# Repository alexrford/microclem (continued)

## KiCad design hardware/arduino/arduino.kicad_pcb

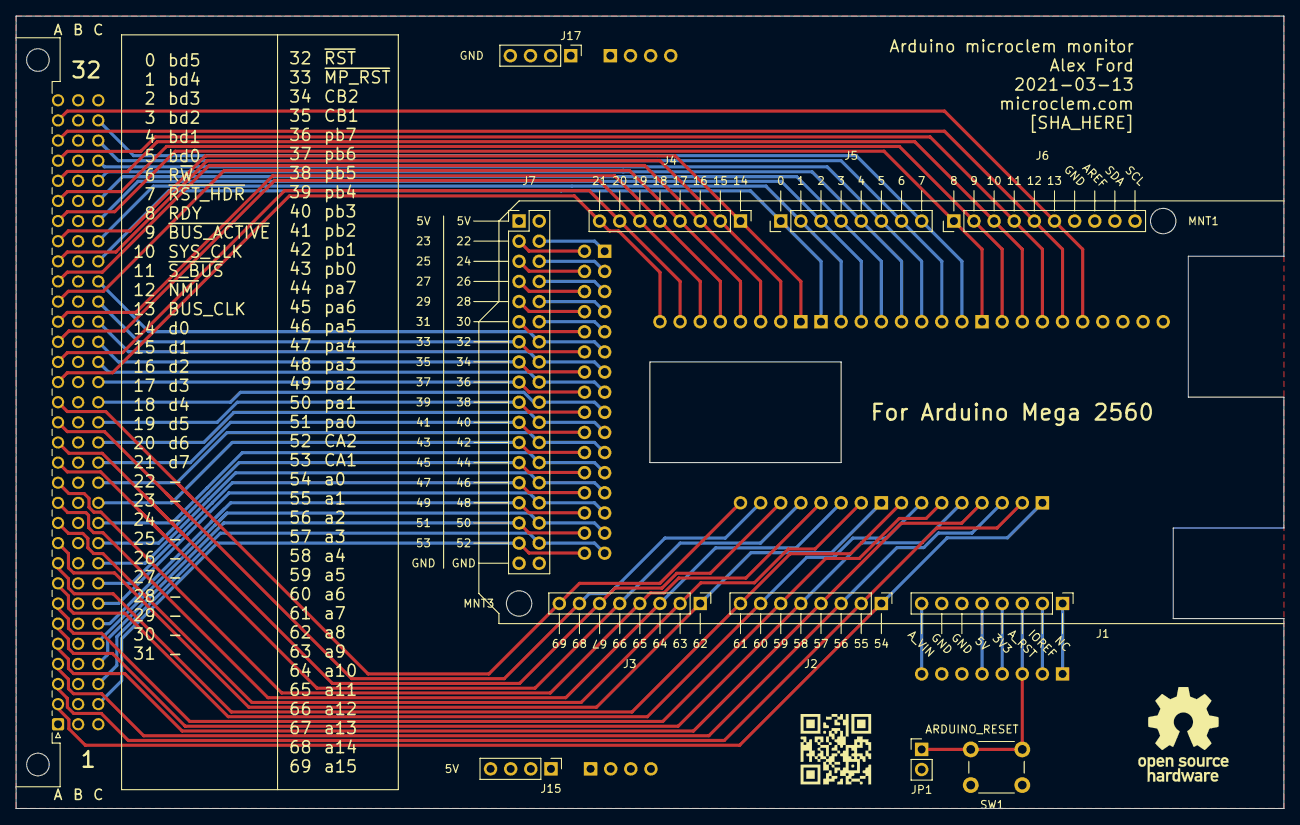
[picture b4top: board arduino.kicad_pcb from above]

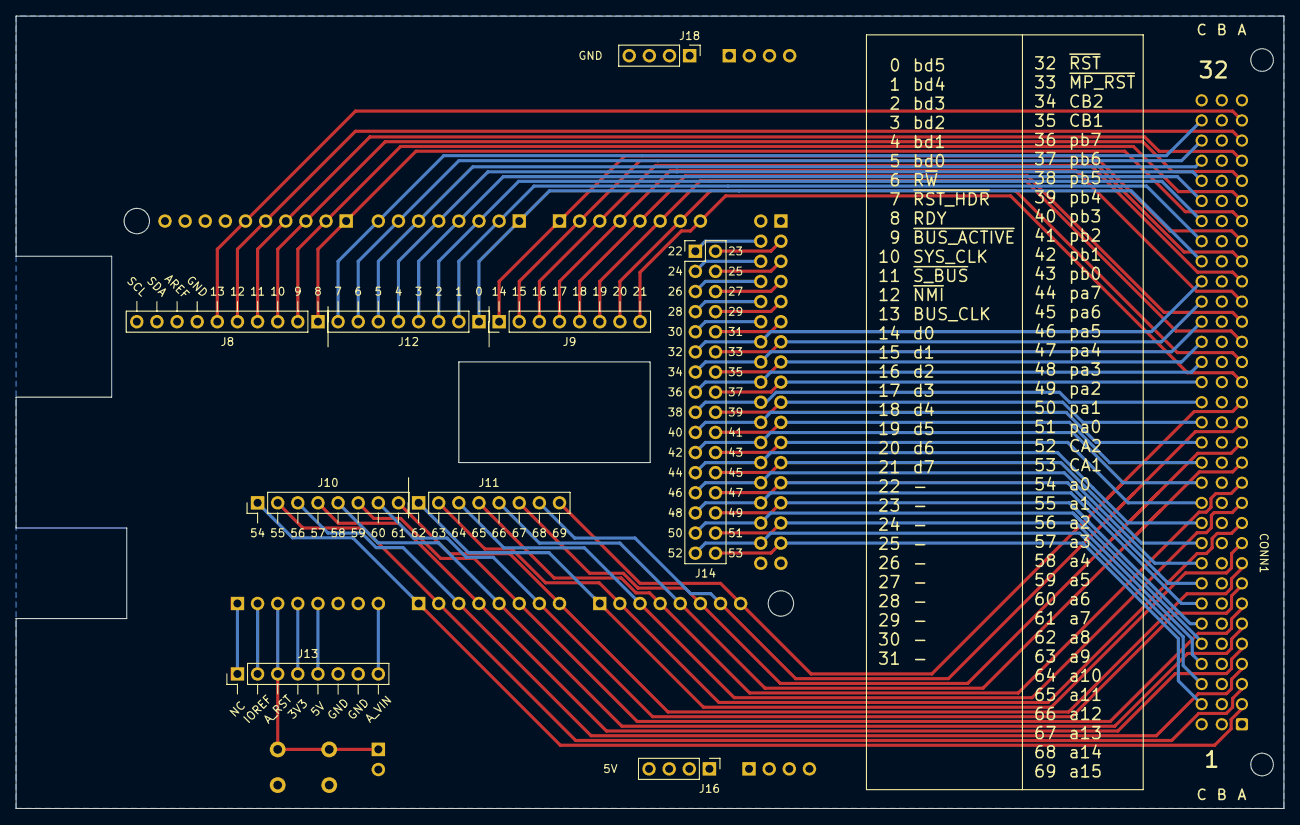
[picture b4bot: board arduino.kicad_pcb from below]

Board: 2 copper layers, 160.0 x 100.0 mm, 23 parts (9 on the bottom side), 78 nets.

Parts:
CONN1: C96ABC; DIN41612_C_3x32_Male_Horizontal_THT_CAPS
J1, J2, J3, J4, J5, J9, J10, J11, J12, J13: Conn_01x08_Male; PinHeader_1x08_P2.54mm_Vertical
J6, J8: Conn_01x10_Male; PinHeader_1x10_P2.54mm_Vertical
J7: Conn_02x18_Odd_Even; PinHeader_2x18_P2.54mm_Vertical
J14: Conn_02x16_Odd_Even; PinHeader_2x16_P2.54mm_Vertical
J15, J16, J17, J18: Conn_02x02_Odd_Even; PinHeader_1x04_P2.54mm_Vertical
JP1: Jumper_2_Open; PinHeader_1x02_P2.54mm_Vertical
MNT1, MNT3: MountingHole_3.2mm_M3
SW1: SW_Push; SW_PUSH_6mm

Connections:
0: CONN1.C24, J5.1, J12.1
1: CONN1.C25, J5.2, J12.2
2: CONN1.C26, J5.3, J12.3
3: CONN1.C27, J5.4, J12.4
4: CONN1.C28, J5.5, J12.5
5: CONN1.C29, J5.6, J12.6
6: CONN1.C30, J5.7, J12.7
7: CONN1.C31, J5.8, J12.8
8: CONN1.A26, J6.1, J8.1
9: CONN1.A27, J6.2, J8.2
10: CONN1.A28, J6.3, J8.3
11: CONN1.A29, J6.4, J8.4
12: CONN1.A30, J6.5, J8.5
13: CONN1.A31, J6.6, J8.6
14: CONN1.A25, J4.1, J9.1
15: CONN1.A24, J4.2, J9.2
16: CONN1.A23, J4.3, J9.3
17: CONN1.A22, J4.4, J9.4
18: CONN1.A21, J4.5, J9.5
19: CONN1.A20, J4.6, J9.6
20: CONN1.A19, J4.7, J9.7
21: CONN1.A18, J4.8, J9.8
22: J7.4, J14.1
23: J7.3, J14.2
24: J7.6, J14.3
25: J7.5, J14.4
26: J7.8, J14.5
27: J7.7, J14.6
28: J7.10, J14.7
29: J7.9, J14.8
30: J7.12, J14.9
31: J7.11, J14.10
32: CONN1.C23, J7.14, J14.11
33: CONN1.C22, J7.13, J14.12
34: CONN1.C21, J7.16, J14.13
35: CONN1.C20, J7.15, J14.14
36: CONN1.C19, J7.18, J14.15
37: CONN1.C18, J7.17, J14.16
38: CONN1.C17, J7.20, J14.17
39: CONN1.C16, J7.19, J14.18
40: CONN1.C15, J7.22, J14.19
41: CONN1.C14, J7.21, J14.20
42: CONN1.C13, J7.24, J14.21
43: CONN1.C12, J7.23, J14.22
44: CONN1.C11, J7.26, J14.23
45: CONN1.C10, J7.25, J14.24
46: CONN1.C9, J7.28, J14.25
47: CONN1.C8, J7.27, J14.26
48: CONN1.C7, J7.30, J14.27
49: CONN1.C6, J7.29, J14.28
50: CONN1.C5, J7.32, J14.29
51: CONN1.C4, J7.31, J14.30
52: CONN1.C3, J7.34, J14.31
53: CONN1.C2, J7.33, J14.32
54: CONN1.A2, J2.1, J10.1
55: CONN1.A3, J2.2, J10.2
56: CONN1.A4, J2.3, J10.3
57: CONN1.A5, J2.4, J10.4
58: CONN1.A6, J2.5, J10.5
59: CONN1.A7, J2.6, J10.6
60: CONN1.A8, J2.7, J10.7
61: CONN1.A9, J2.8, J10.8
62: CONN1.A10, J3.1, J11.1
63: CONN1.A11, J3.2, J11.2
64: CONN1.A12, J3.3, J11.3
65: CONN1.A13, J3.4, J11.4
66: CONN1.A14, J3.5, J11.5
67: CONN1.A15, J3.6, J11.6
68: CONN1.A16, J3.7, J11.7
69: CONN1.A17, J3.8, J11.8
+5V: CONN1.A1, CONN1.B1, CONN1.C1, J15.1, J15.2, J15.3, J15.4, J16.1, J16.2, J16.3, J16.4
A_3V3: J1.4, J13.4
A_5V: J1.5, J13.5
A_RESET: J1.3, J13.3, JP1.1, SW1.1
A_VIN: J1.8, J13.8
GND: CONN1.A32, CONN1.B32, CONN1.C32, J1.6, J1.7, J6.7, J7.35, J7.36, J13.6, J13.7, J17.1, J17.2, J17.3, J17.4, J18.1, J18.2, J18.3, J18.4, JP1.2, SW1.2
IOREF: J1.2, J13.2
NC: J1.1, J13.1

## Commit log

2021-03-01 gitignore
2021-03-01 initial version of base board
2021-03-01 LICENSE.txt
2021-03-01 board renders
2021-03-01 remove an unused library
2021-03-01 README.md
2021-03-09 start on a backplane design
2021-03-11 start designing an arduino debug board
2021-03-12 arduino: add more headers and annotations
2021-03-13 arduino: add annotations and some pins
2021-03-13 arduino: credits
2021-03-13 arduino: minor tweaks
2021-03-13 backplane: fix spacing to use 5.08mm HP, expand to 8 back slots with 3/4 spacing
2021-03-13 base: update specific 74 part references
2021-03-13 don't gitignore bom files
2021-03-13 base: generate bom
2021-03-13 clean up bom
2021-03-13 label BASE_CLK signal
2021-03-13 move BASE_CLK signal
2021-03-14 start to put clock hardware on the backplane
2021-03-14 backplane: shrink by 1mm in both dimensions and start rearranging components
2021-03-15 backplane: remove the base/bus clock switch
2021-03-15 backplane: move a track
2021-03-17 backplane: bump some clearance hole diameters
2021-03-19 backplane: use less mounting hardware
2021-03-20 backplane: 4 screw bars to 2
2021-03-20 backplane: change some parts to SMD (WIP)
2021-03-20 backplane: use mostly SMD parts
2021-03-23 backplane: place traces
2021-03-27 backplane: tweak mounting holes
2021-03-27 models: add a basic cad model of the case
2021-03-28 models: cleanup whitespace
2021-03-28 models: fix indentation
2021-03-28 models: add a front panel lcd
2021-03-28 backplane: reduce mounting hardware used
2021-03-28 models: fix whitespace and indentation
2021-03-28 models: bump the backplane size
2021-03-29 models: simplify how the backplane is secured
2021-04-06 models: add a basic front panel pcb
2021-04-07 models: add connectors for backplane to fp
2021-05-09 backplane: add soft power on/off circuit to backplane
2021-05-09 backplane: make some diodes through hole
2021-05-09 backplane: add a logo
2021-05-09 backplane: minor improvements
2021-06-08 start adding reverse voltage protection
2021-06-27 backplane: fix some values and footprints
2021-06-27 backplane: remove fuse
2021-06-27 document existing bus signals properly in backplane
2021-06-27 more backplane comments
2021-06-27 some base board comments
2021-07-10 backplane tweaks
2021-07-10 update schematics for backplane and base to put PHI_2 on the bus
2021-07-10 base: relayout WIP
2021-07-10 base: smaller keepout area
2021-07-11 base: slightly simplify and fix schematic
2021-07-12 base: first pass at re-routing
2021-07-12 start on a connector between the front panel and the backplane
2021-07-12 slightly increase ground plane coverage
2021-07-14 base: route optimization, label positioning
2021-07-14 base: big logo
2021-07-15 base: move a trace
2022-02-13 shift fp connector to other side of backplane
2022-02-13 backplane relayout 1
2022-02-13 placeholder front panel and fp_bp connection
2022-02-13 backplane misc
2022-02-13 front panel - backplane connector
2022-02-13 base: mounting holes
2022-02-14 small qr code
2022-02-14 bp_fp connector improvements
2022-02-14 front panel connector placement and lcd
2022-02-14 copy graphics lib
2022-02-15 FP WIP
2022-02-16 front panel: nhd-0440wh 4x40 panel
